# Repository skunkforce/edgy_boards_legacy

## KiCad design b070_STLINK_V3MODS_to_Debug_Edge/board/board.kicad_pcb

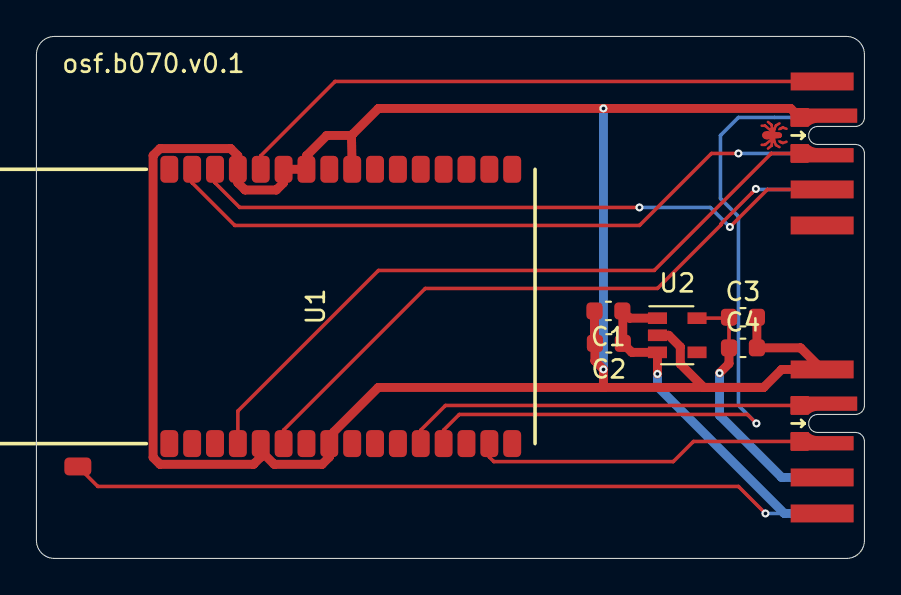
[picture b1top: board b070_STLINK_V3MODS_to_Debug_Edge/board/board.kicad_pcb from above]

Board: 2 copper layers, 46.0 x 29.0 mm, 8 parts (0 on the bottom side), 11 nets.

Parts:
C1: 100nF; C_0603_1608Metric
C2, C4: 1uF; C_0603_1608Metric
C3: 10uF; C_0603_1608Metric
J1: DebugEdge_02x05; debug_edge_2x05_host
J2: 010_UART; on_edge_2x05_host
U1: STLINK-V3MODS; stlink-v3mods
U2: TC1017-xCT; SOT-23-5

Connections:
+3V3: C3.1, C4.1, J2.9, U2.5
+5V: C1.1, C2.1, J2.10, U1.33, U2.1, U2.3
GND: C1.2, C2.2, C3.2, C4.2, J1.1, J2.1, U1.5, U1.8, U1.24, U1.26, U1.27, U1.29, U2.2
unnamed: J1.2, U1.4
unnamed: J1.3, U1.13
unnamed: J1.4, U1.31
unnamed: J1.5, U1.30
unnamed: J1.6, U1.6
unnamed: J1.7, U1.28
unnamed: J2.2, U1.12
unnamed: J2.3, U1.15

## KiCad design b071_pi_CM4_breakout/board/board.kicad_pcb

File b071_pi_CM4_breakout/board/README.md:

# pi Compute Module 4 breakout

## Setting up the CM4 as a remote edgy composition gateway
One important use case of edgyboards is to fascilitate unit testing and CI style development near the metal by effectivly mocking out parts of the hardware.

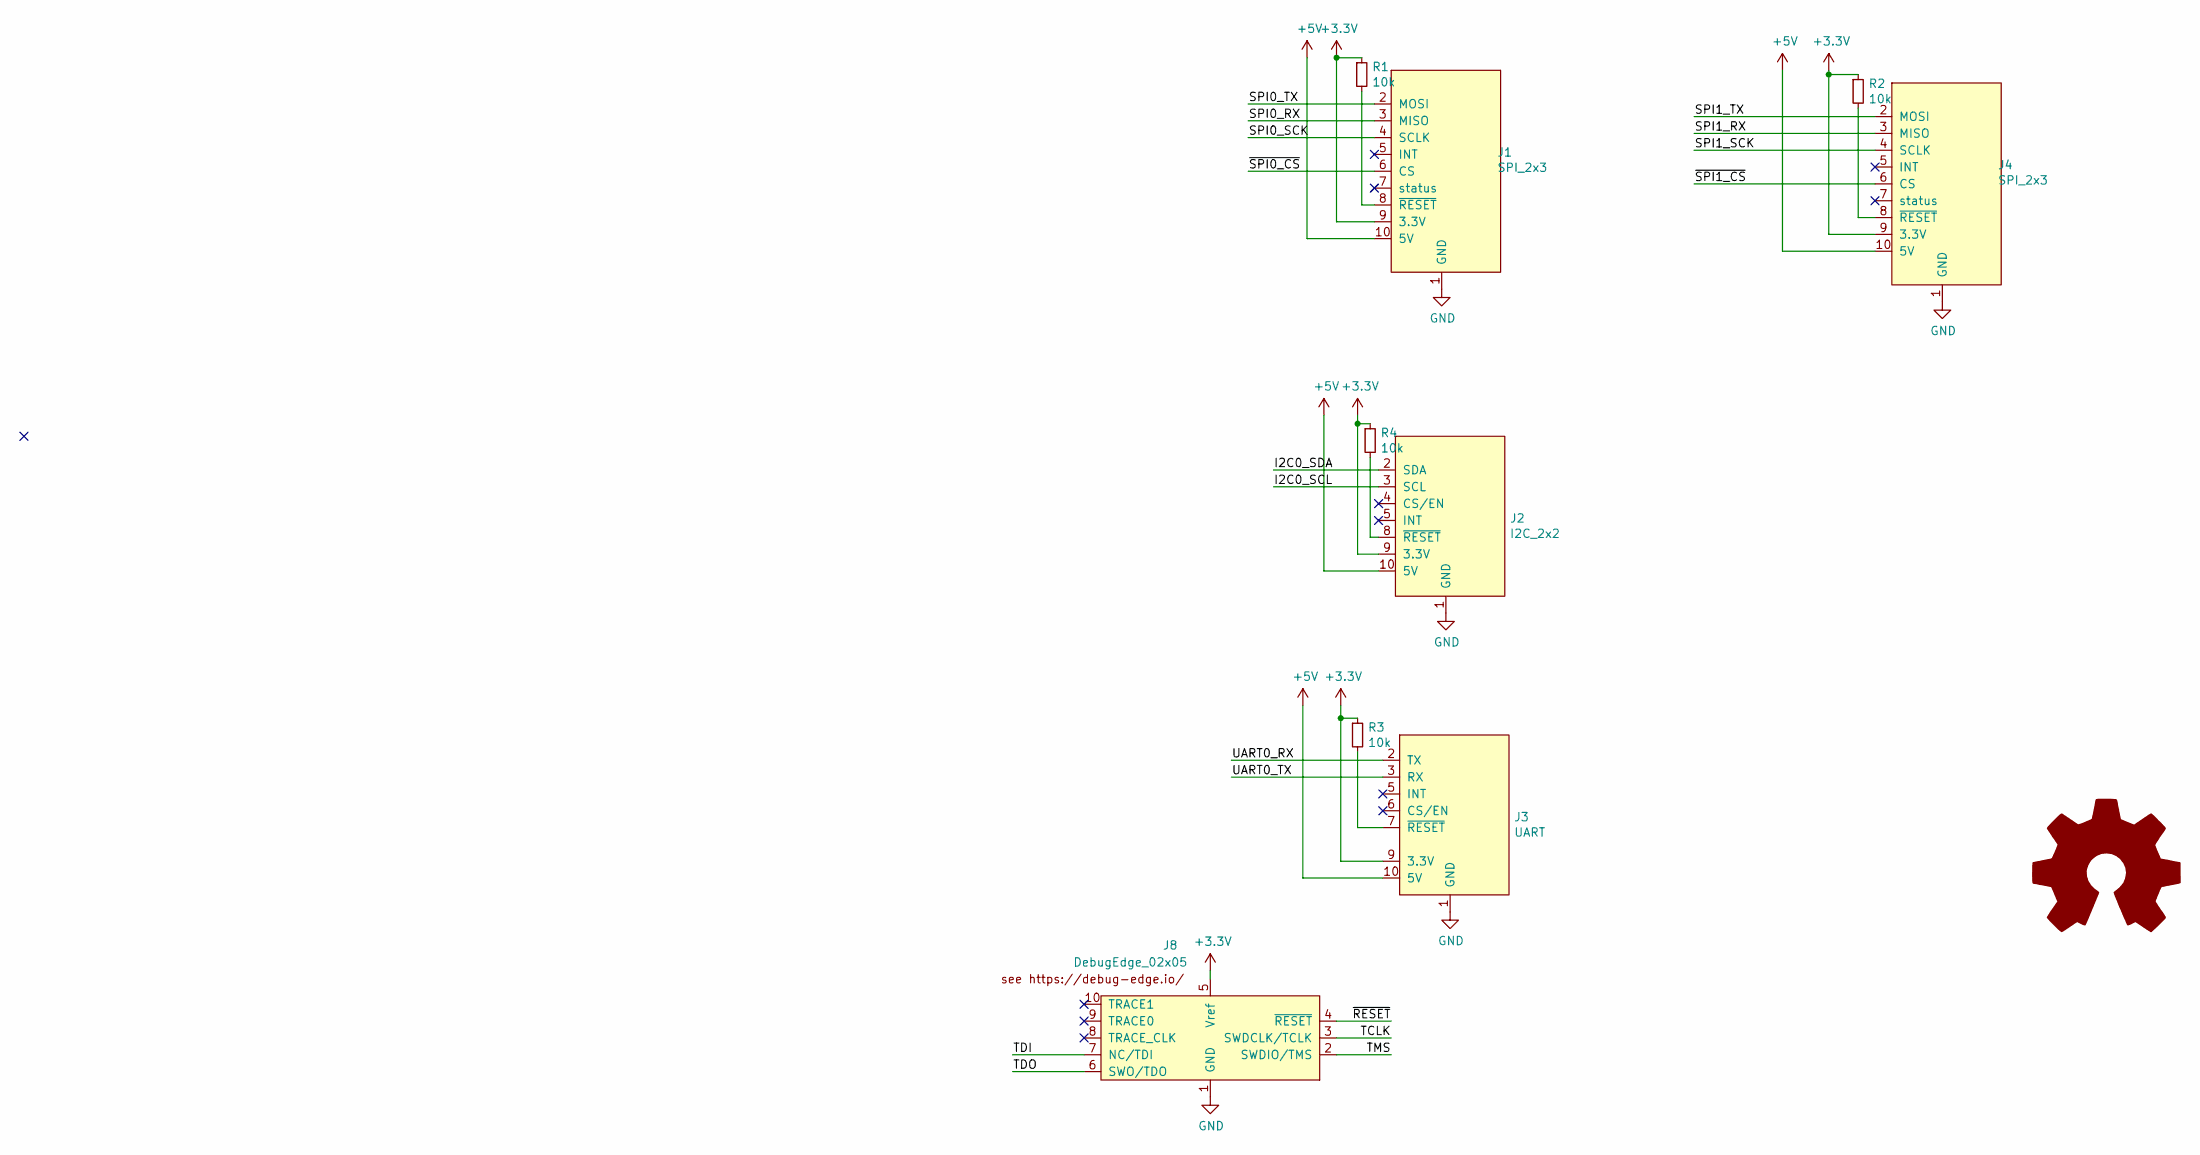
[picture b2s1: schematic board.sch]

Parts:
J1: SPI_2x3; on_edge_2x05_up_host
J2: I2C_2x2; on_edge_2x05_host
J3: UART; on_edge_2x05_host
J4: SPI_2x3; on_edge_2x05_host
J8: DebugEdge_02x05; debug_edge_2x05_host
R1, R2, R3, R4: 10k; R_0603_1608Metric
l1: Logo_Open_Hardware_Large; OSHW-Logo2_7.3x6mm_SilkScreen

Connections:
+3V3: J1.9 (3.3V), J2.9 (3.3V), J3.9 (3.3V), J4.9 (3.3V), J8.5 (Vref), R1.1, R2.1, R3.1, R4.1
+5V: J1.10 (5V), J2.10 (5V), J3.10 (5V), J4.10 (5V)
/I2C0_SCL: J2.3 (SCL)
/I2C0_SDA: J2.2 (SDA)
/SPI0_RX: J1.3 (MISO)
/SPI0_SCK: J1.4 (SCLK)
/SPI0_TX: J1.2 (MOSI)
/SPI1_RX: J4.3 (MISO)
/SPI1_SCK: J4.4 (SCLK)
/SPI1_TX: J4.2 (MOSI)
/TCLK: J8.3 (SWDCLK/TCLK)
/TDI: J8.7 (NC/TDI)
/TDO: J8.6 (SWO/TDO)
/TMS: J8.2 (SWDIO/TMS)
/UART0_RX: J3.2 (TX)
/UART0_TX: J3.3 (RX)
/~RESET: J8.4 (~RESET~)
/~SPI0_CS: J1.6 (CS)
/~SPI1_CS: J4.6 (CS)
GND: J1.1 (GND), J2.1 (GND), J3.1 (GND), J4.1 (GND), J8.1 (GND)
unnamed: J1.8 (~RESET), R1.2
unnamed: J2.8 (~RESET), R4.2
unnamed: J3.7 (~RESET), R3.2
unnamed: J4.8 (~RESET), R2.2

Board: 2 copper layers, 10 parts (1 on the bottom side), 7 nets, no tracks yet.

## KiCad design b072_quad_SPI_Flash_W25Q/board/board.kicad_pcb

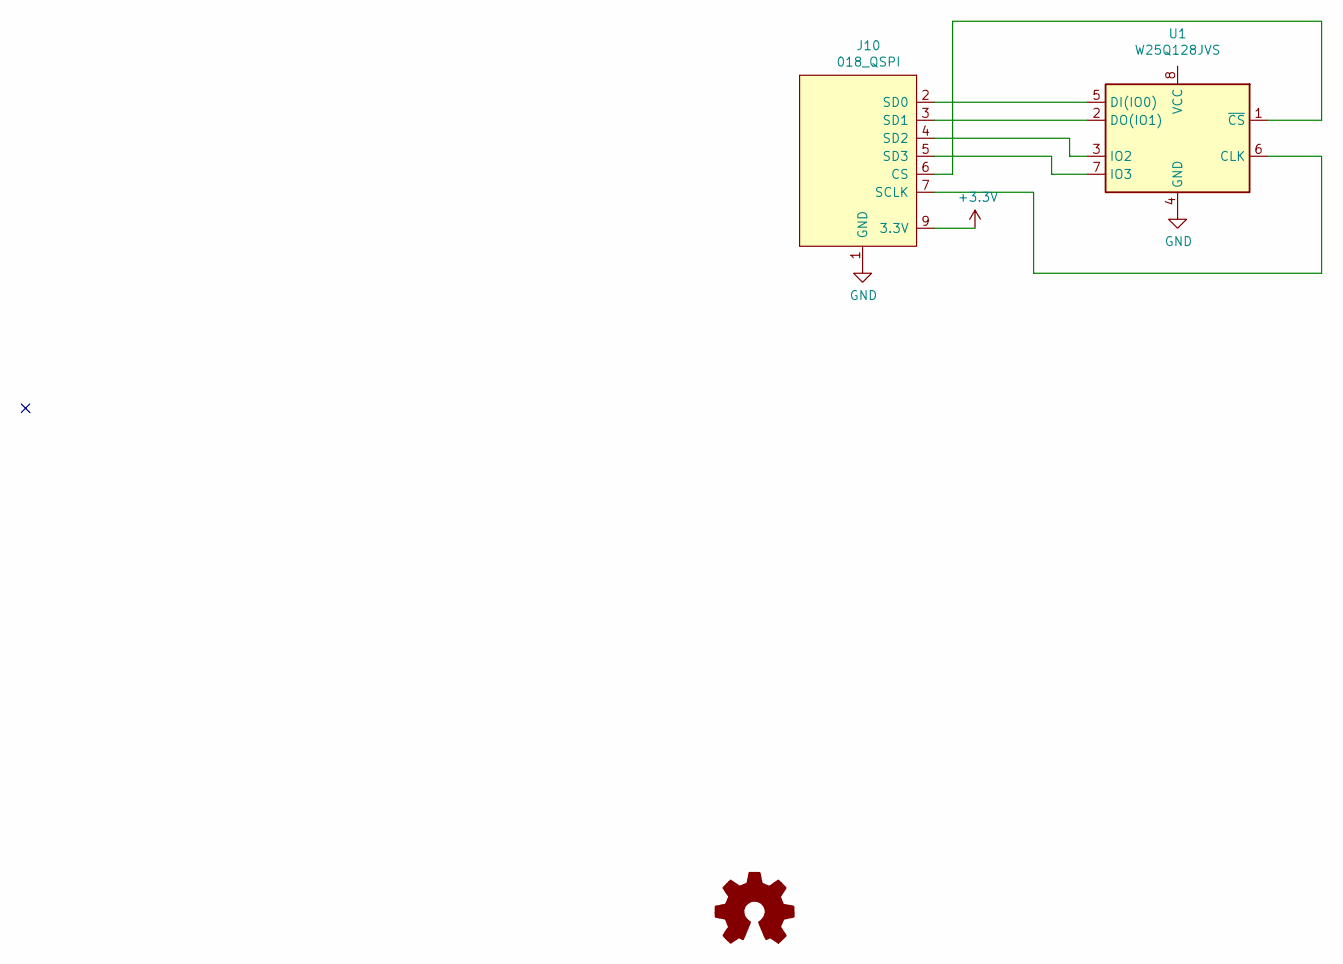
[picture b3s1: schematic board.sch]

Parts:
J10: 018_QSPI; on_edge_2x05_device
LOGO1: Logo_Open_Hardware_Small; OSHW-Logo2_9.8x8mm_SilkScreen
U1: W25Q128JVS; SOIC-8_5.23x5.23mm_P1.27mm; MPN W25Q16JVSNIQ

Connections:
+3V3: J10.9 (3.3V)
GND: J10.1 (GND), U1.4 (GND)
unnamed: J10.2 (SD0), U1.5 (DI(IO0))
unnamed: J10.3 (SD1), U1.2 (DO(IO1))
unnamed: J10.4 (SD2), U1.3 (IO2)
unnamed: J10.5 (SD3), U1.7 (IO3)
unnamed: J10.6 (CS), U1.1 (~CS)
unnamed: J10.7 (SCLK), U1.6 (CLK)

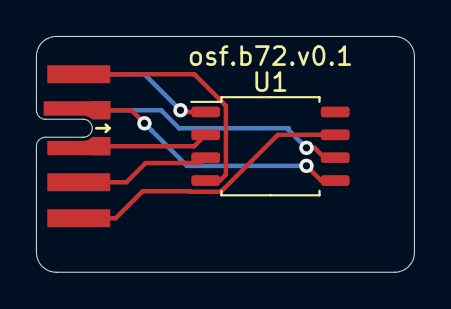
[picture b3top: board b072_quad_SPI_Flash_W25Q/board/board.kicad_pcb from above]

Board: 4 copper layers, 21.0 x 13.1 mm, 3 parts (1 on the bottom side), 7 nets.

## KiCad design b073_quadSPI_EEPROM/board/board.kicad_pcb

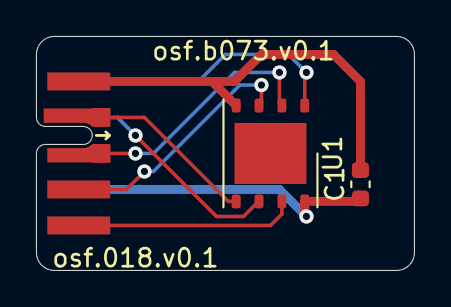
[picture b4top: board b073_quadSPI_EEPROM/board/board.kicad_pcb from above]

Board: 2 copper layers, 21.0 x 13.0 mm, 3 parts (0 on the bottom side), 8 nets.

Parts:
C1: 100nF; C_0603_1608Metric
J1: 018_QSPI; on_edge_2x05_device
U1: W25Q32JVSS; WSON-8-1EP_6x5mm_P1.27mm_EP3.4x4mm

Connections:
GND: C1.2, J1.1 (GND), U1.4 (GND)
unnamed: C1.1, J1.9 (3.3V), U1.8 (VCC)
unnamed: J1.2 (SD0), U1.5 (DI(IO0))
unnamed: J1.3 (SD1), U1.2 (DO(IO1))
unnamed: J1.4 (SD2), U1.3 (IO2)
unnamed: J1.5 (SD3), U1.7 (IO3)
unnamed: J1.6 (CS), U1.1 (~CS)
unnamed: J1.7 (SCLK), U1.6 (CLK)

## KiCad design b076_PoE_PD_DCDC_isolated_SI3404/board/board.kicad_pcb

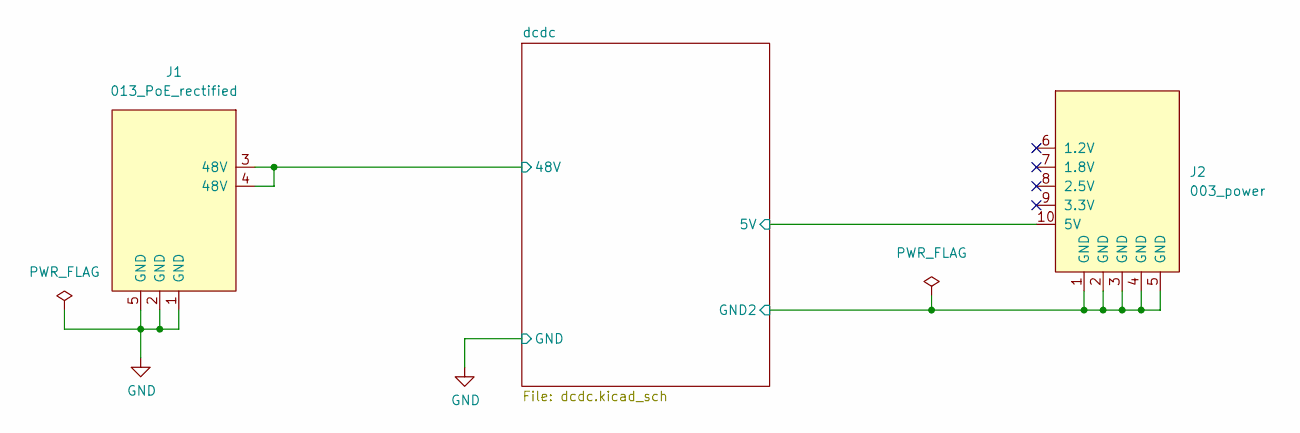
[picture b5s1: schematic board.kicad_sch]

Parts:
J1: 013_PoE_rectified; on_edge_2x05_device
J2: 003_power; on_edge_2x05_host

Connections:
/dcdc/5V: J2.10 (5V); also elsewhere on the board
/dcdc/48V: J1.3 (48V), J1.4 (48V); also elsewhere on the board
/dcdc/GND2: J2.1 (GND), J2.2 (GND), J2.3 (GND), J2.4 (GND), J2.5 (GND); also elsewhere on the board
GND: J1.1 (GND), J1.2 (GND), J1.5 (GND); also elsewhere on the board

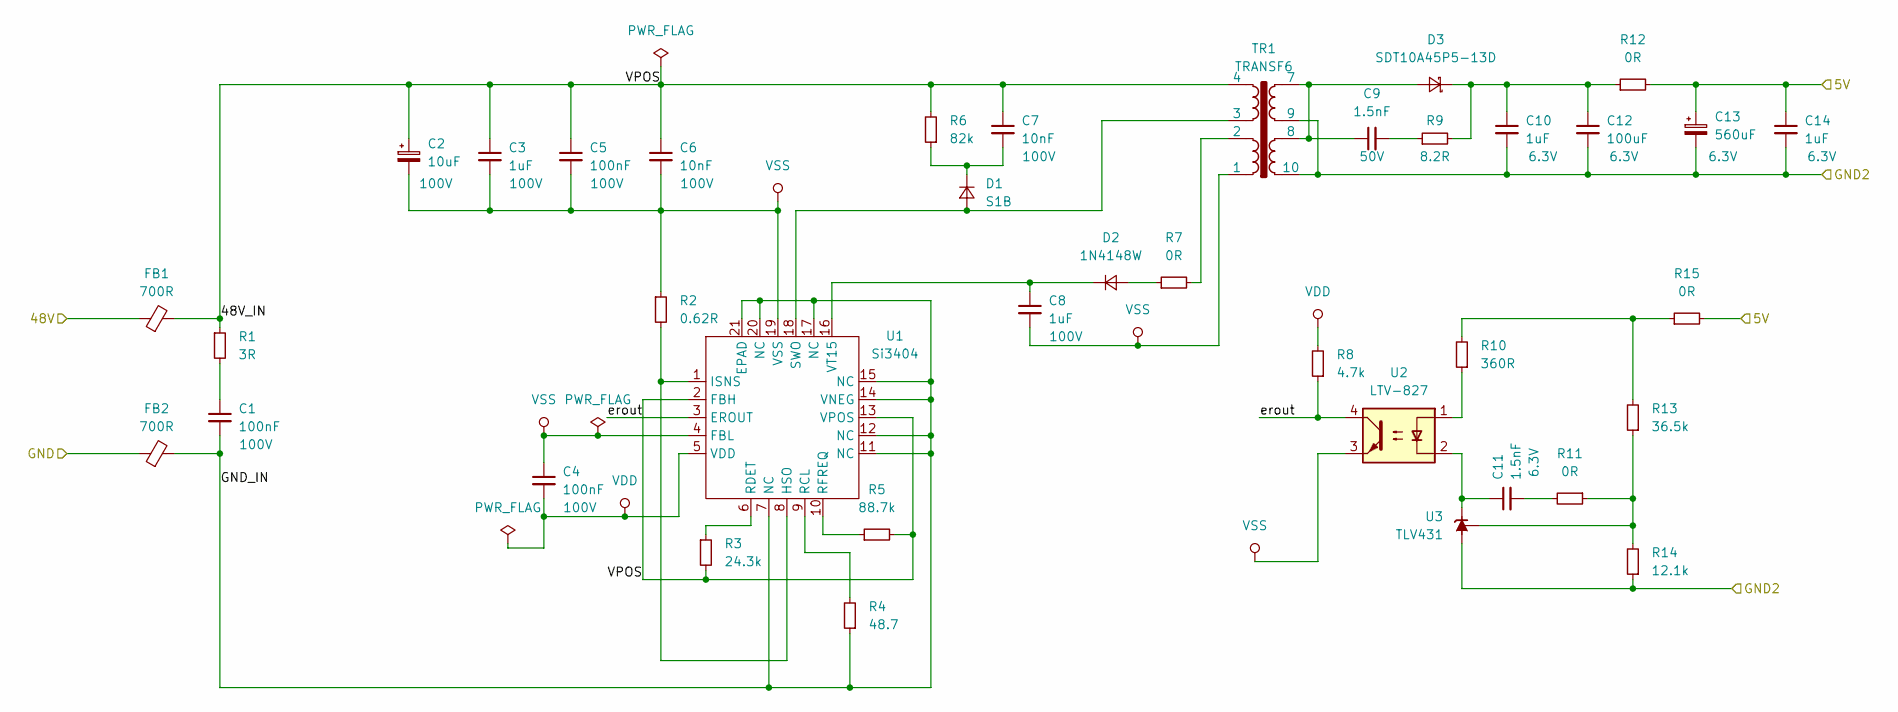
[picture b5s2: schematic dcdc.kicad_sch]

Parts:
C1, C5: 100nF; C_1210_3225Metric; Voltage 100V
C2: 10uF; CP_Elec_10x10; Voltage 100V
C3, C8: 1uF; C_1210_3225Metric; Voltage 100V
C4: 100nF; C_0603_1608Metric; Voltage 100V
C6, C7: 10nF; C_1210_3225Metric; Voltage 100V
C9: 1.5nF; C_0805_2012Metric; Voltage 50V
C10, C14: 1uF; C_0603_1608Metric; Voltage 6.3V
C11: 1.5nF; C_0603_1608Metric; Voltage 6.3V
C12: 100uF; C_0805_2012Metric; Voltage 6.3V
C13: 560uF; CP_Elec_10x10; Voltage 6.3V
D1: S1B; D_SMB
D2: 1N4148W; D_SOD-123; MPN 1N4148W-HF
D3: SDT10A45P5-13D; D_PowerDI-5; MPN SDT10A45P5-13D
FB1, FB2: 700R; L_0805_2012Metric; MPN 742792040
R1: 3R; R_0603_1608Metric
R2: 0.62R; R_0805_2012Metric
R3: 24.3k; R_0603_1608Metric
R4: 48.7; R_0603_1608Metric
R5: 88.7k; R_0603_1608Metric
R6: 82k; R_0603_1608Metric
R7, R11, R15: 0R; R_0603_1608Metric
R8: 4.7k; R_0603_1608Metric
R9: 8.2R; R_0603_1608Metric
R10: 360R; R_0603_1608Metric
R12: 0R; R_1210_3225Metric
R13: 36.5k; R_0603_1608Metric
R14: 12.1k; R_0603_1608Metric
TR1: TRANSF6; EP13_SMT_H_10PIN_(2381); MPN 749119950
U1: Si3404; QFN-20-1EP_4x4mm_P0.5mm_EP2.5x2.5mm_ThermalVias; MPN SI3404-A-GM
U2: LTV-827; DIP-8_W7.62mm; MPN FOD817A3SD
U3: TLV431; SOT-23; MPN TLV431CSN1T1G

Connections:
/dcdc/5V: C13.1, C14.1, R12.2, R15.2; also elsewhere on the board
/dcdc/48V: FB1.1; also elsewhere on the board
/dcdc/48V_IN: C2.1, C3.1, C5.1, C6.1, C7.1, FB1.2, R1.1, R3.2, R5.2, R6.2, TR1.4, U1.2 (FBH), U1.13 (VPOS)
/dcdc/GND2: C10.2, C12.2, C13.2, C14.2, R14.1, TR1.9, TR1.10, U3.3 (A); also elsewhere on the board
/dcdc/GND_IN: C1.2, FB2.2, R4.1, U1.7 (NC), U1.11 (NC), U1.12 (NC), U1.14 (VNEG), U1.15 (NC), U1.17 (NC), U1.20 (NC), U1.21 (EPAD)
/dcdc/erout: R8.1, U1.3 (EROUT), U2.4
GND: FB2.1; also elsewhere on the board
unnamed: C1.1, R1.2
unnamed: C7.2, D1.1 (K), R6.1
unnamed: C8.1, D2.1 (K), U1.16 (VT15)
unnamed: C9.1, D3.2 (A), TR1.7, TR1.8
unnamed: C9.2, R9.1
unnamed: C10.1, C12.1, D3.1 (K), R9.2, R12.1
unnamed: C11.1, U2.2, U3.1 (K)
unnamed: C11.2, R11.2
unnamed: D1.2 (A), TR1.3, U1.18 (SWO)
unnamed: D2.2 (A), R7.1
unnamed: R2.2, U1.1 (ISNS), U1.8 (HSO)
unnamed: R3.1, U1.6 (RDET)
unnamed: R4.2, U1.9 (RCL)
unnamed: R5.1, U1.10 (RFREQ)
unnamed: R7.2, TR1.2
unnamed: R10.1, U2.1
unnamed: R10.2, R13.2, R15.1
unnamed: R11.1, R13.1, R14.2, U3.2 (REF)
VDD: C4.2, R8.2, U1.5 (VDD)
VSS: C2.2, C3.2, C4.1, C5.2, C6.2, C8.2, R2.1, TR1.1, U1.4 (FBL), U1.19 (VSS), U2.3

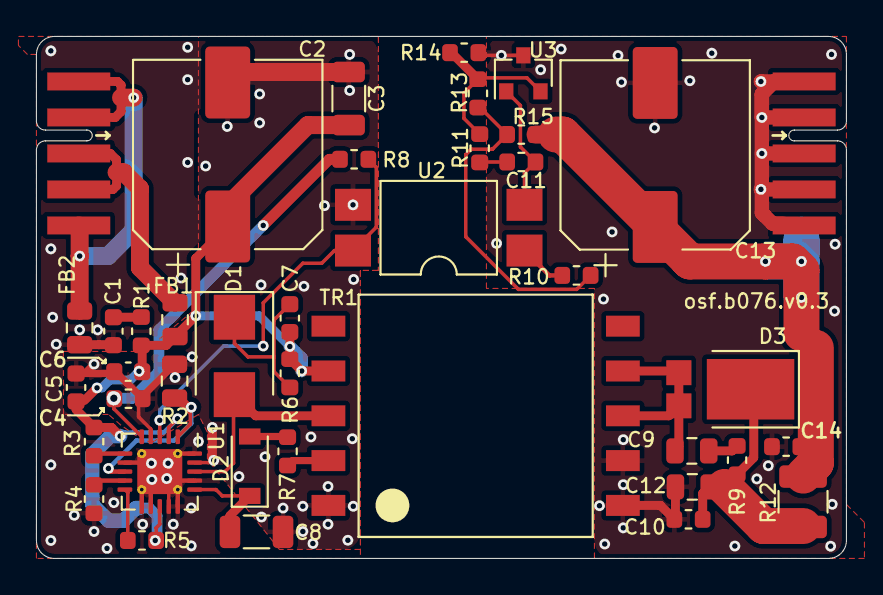
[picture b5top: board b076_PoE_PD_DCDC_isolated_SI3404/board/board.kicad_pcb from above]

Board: 2 copper layers, 45.0 x 29.0 mm, 40 parts (0 on the bottom side), 27 nets.

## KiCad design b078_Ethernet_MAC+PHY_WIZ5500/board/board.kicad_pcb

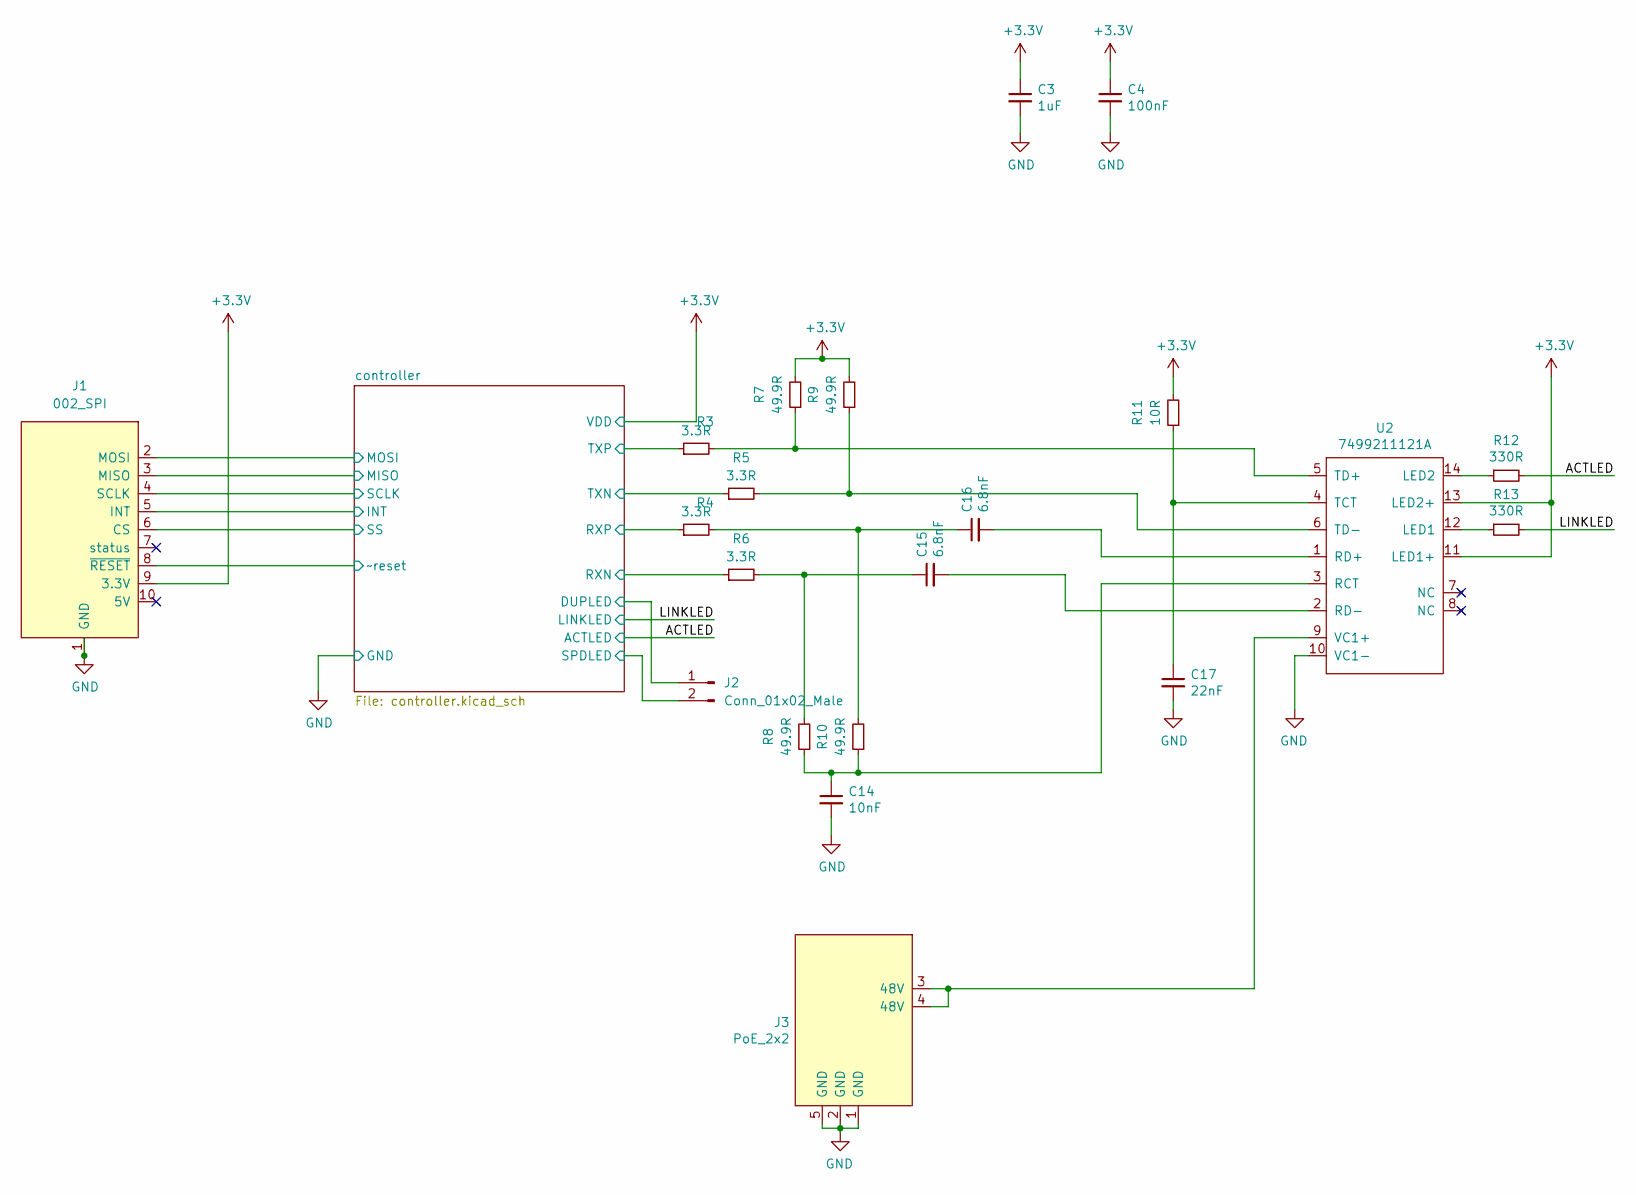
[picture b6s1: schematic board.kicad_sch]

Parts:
C3: 1uF; C_0603_1608Metric; Voltage 6.3V
C4: 100nF; C_0603_1608Metric; Voltage 6.3V
C14: 10nF; C_0603_1608Metric; Voltage 6.3V
C15, C16: 6.8nF; C_0603_1608Metric; Voltage 6.3V
C17: 22nF; C_0603_1608Metric; Voltage 6.3V
J1: 002_SPI; on_edge_2x05_device
J2: Conn_01x02_Male; PinHeader_1x02_P2.54mm_Vertical
J3: PoE_2x2; on_edge_2x05_host
R3, R4, R5, R6: 3.3R; R_0603_1608Metric
R7, R8, R9, R10: 49.9R; R_0805_2012Metric
R11: 10R; R_0805_2012Metric
R12, R13: 330R; R_0603_1608Metric
U2: 7499211121A; MPN 7499211121A

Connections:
+3V3: C3.1, C4.1, J1.9 (3.3V), R7.2, R9.2, R11.2, U2.11 (LED1+), U2.13 (LED2+); also elsewhere on the board
/ACTLED: R12.2; also elsewhere on the board
/LINKLED: R13.2; also elsewhere on the board
/controller/DUPLED: J2.1; also elsewhere on the board
/controller/INT: J1.5 (INT); also elsewhere on the board
/controller/MISO: J1.3 (MISO); also elsewhere on the board
/controller/MOSI: J1.2 (MOSI); also elsewhere on the board
/controller/RXN: R6.1; also elsewhere on the board
/controller/RXP: R4.1; also elsewhere on the board
/controller/SCLK: J1.4 (SCLK); also elsewhere on the board
/controller/SPDLED: J2.2; also elsewhere on the board
/controller/SS: J1.6 (CS); also elsewhere on the board
/controller/TXN: R5.1; also elsewhere on the board
/controller/TXP: R3.1; also elsewhere on the board
/controller/~reset: J1.8 (~RESET); also elsewhere on the board
GND: C3.2, C4.2, C14.2, C17.2, J1.1 (GND), J3.1 (GND), J3.2 (GND), J3.5 (GND), U2.10 (VC1-); also elsewhere on the board
unnamed: C14.1, R8.1, R10.1, U2.3 (RCT)
unnamed: C15.1, R6.2, R8.2
unnamed: C15.2, U2.2 (RD-)
unnamed: C16.1, R4.2, R10.2
unnamed: C16.2, U2.1 (RD+)
unnamed: C17.1, R11.1, U2.4 (TCT)
unnamed: J3.3 (48V), J3.4 (48V), U2.9 (VC1+)
unnamed: R3.2, R7.1, U2.5 (TD+)
unnamed: R5.2, R9.1, U2.6 (TD-)
unnamed: R12.1, U2.14 (LED2)
unnamed: R13.1, U2.12 (LED1)

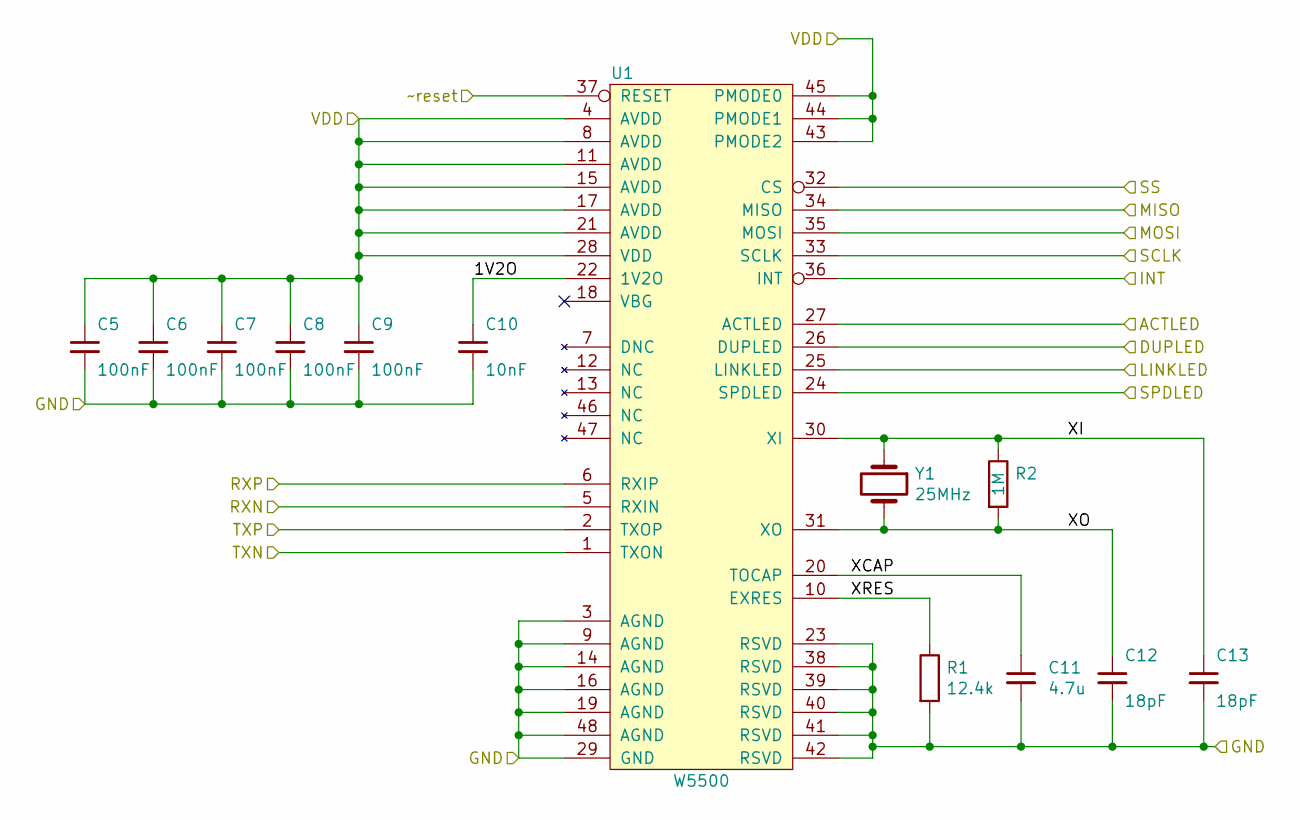
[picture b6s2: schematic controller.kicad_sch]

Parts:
C5, C6, C7, C8, C9: 100nF; C_0603_1608Metric; DigiKey Part Number 1276-1012-1-ND
C10: 10nF; C_0603_1608Metric; DigiKey Part Number 1276-1921-1-ND
C11: 4.7u; C_0603_1608Metric; DigiKey Part Number 1276-1907-1-ND
C12, C13: 18pF; C_0603_1608Metric; DigiKey Part Number 1276-1089-1-ND
R1: 12.4k; R_0603_1608Metric; Tolerance ±1%; DigiKey Part Number 311-12.4KHRCT-ND
R2: 1M; R_0603_1608Metric; DigiKey Part Number 311-1.0MGRCT-ND
U1: W5500; LQFP-48_7x7mm_P0.5mm; DigiKey Part Number 1278-1021-ND
Y1: 25MHz; Crystal_SMD_5032-2Pin_5.0x3.2mm; MPN 445I23D25M00000; DigiKey Part Number CTX1175TR-ND

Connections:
+3V3: C5.1, C6.1, C7.1, C8.1, C9.1, U1.4 (AVDD), U1.8 (AVDD), U1.11 (AVDD), U1.15 (AVDD), U1.17 (AVDD), U1.21 (AVDD), U1.28 (VDD), U1.43 (PMODE2), U1.44 (PMODE1), U1.45 (PMODE0); also elsewhere on the board
/ACTLED: U1.27 (ACTLED); also elsewhere on the board
/LINKLED: U1.25 (LINKLED); also elsewhere on the board
/controller/1V2O: C10.1, U1.22 (1V2O)
/controller/DUPLED: U1.26 (DUPLED); also elsewhere on the board
/controller/INT: U1.36 (INT); also elsewhere on the board
/controller/MISO: U1.34 (MISO); also elsewhere on the board
/controller/MOSI: U1.35 (MOSI); also elsewhere on the board
/controller/RXN: U1.5 (RXIN); also elsewhere on the board
/controller/RXP: U1.6 (RXIP); also elsewhere on the board
/controller/SCLK: U1.33 (SCLK); also elsewhere on the board
/controller/SPDLED: U1.24 (SPDLED); also elsewhere on the board
/controller/SS: U1.32 (CS); also elsewhere on the board
/controller/TXN: U1.1 (TXON); also elsewhere on the board
/controller/TXP: U1.2 (TXOP); also elsewhere on the board
/controller/XCAP: C11.1, U1.20 (TOCAP)
/controller/XI: C13.1, R2.1, U1.30 (XI), Y1.1
/controller/XO: C12.1, R2.2, U1.31 (XO), Y1.2
/controller/XRES: R1.1, U1.10 (EXRES)
/controller/~reset: U1.37 (RESET); also elsewhere on the board
GND: C5.2, C6.2, C7.2, C8.2, C9.2, C10.2, C11.2, C12.2, C13.2, R1.2, U1.3 (AGND), U1.9 (AGND), U1.14 (AGND), U1.16 (AGND), U1.19 (AGND), U1.23 (RSVD), U1.29 (GND), U1.38 (RSVD), U1.39 (RSVD), U1.40 (RSVD), U1.41 (RSVD), U1.42 (RSVD), U1.48 (AGND); also elsewhere on the board

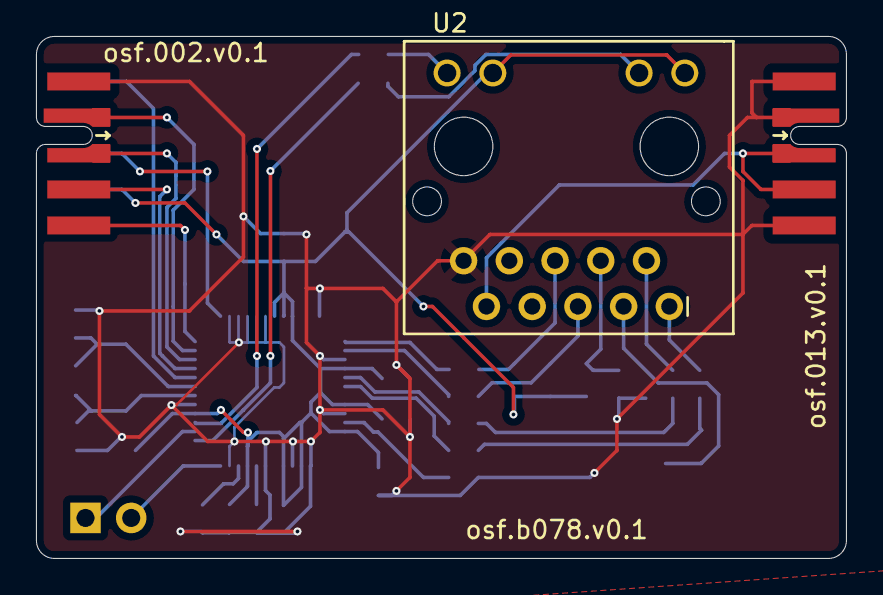
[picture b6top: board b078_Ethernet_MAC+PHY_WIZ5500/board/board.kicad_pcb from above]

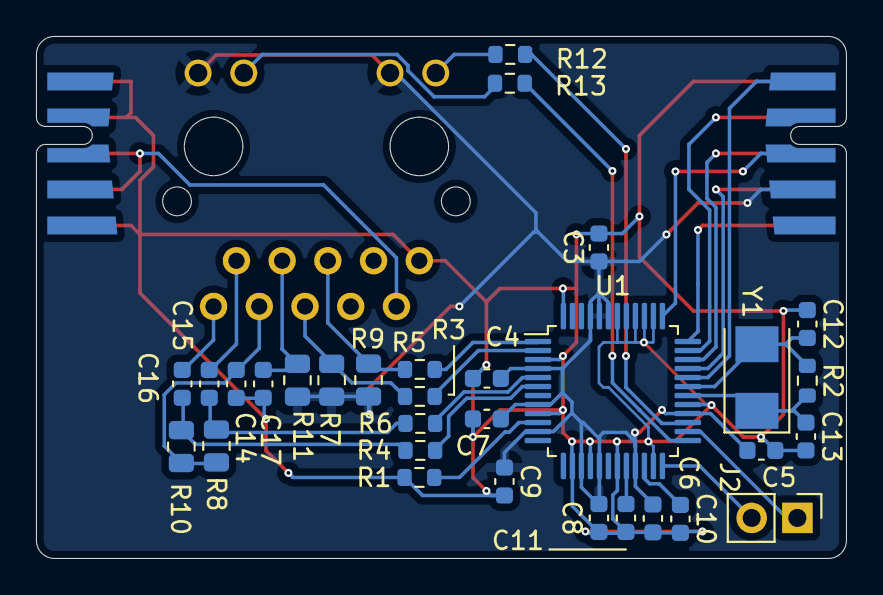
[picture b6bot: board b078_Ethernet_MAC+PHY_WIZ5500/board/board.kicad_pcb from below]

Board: 2 copper layers, 45.0 x 29.0 mm, 34 parts (31 on the bottom side), 32 nets.

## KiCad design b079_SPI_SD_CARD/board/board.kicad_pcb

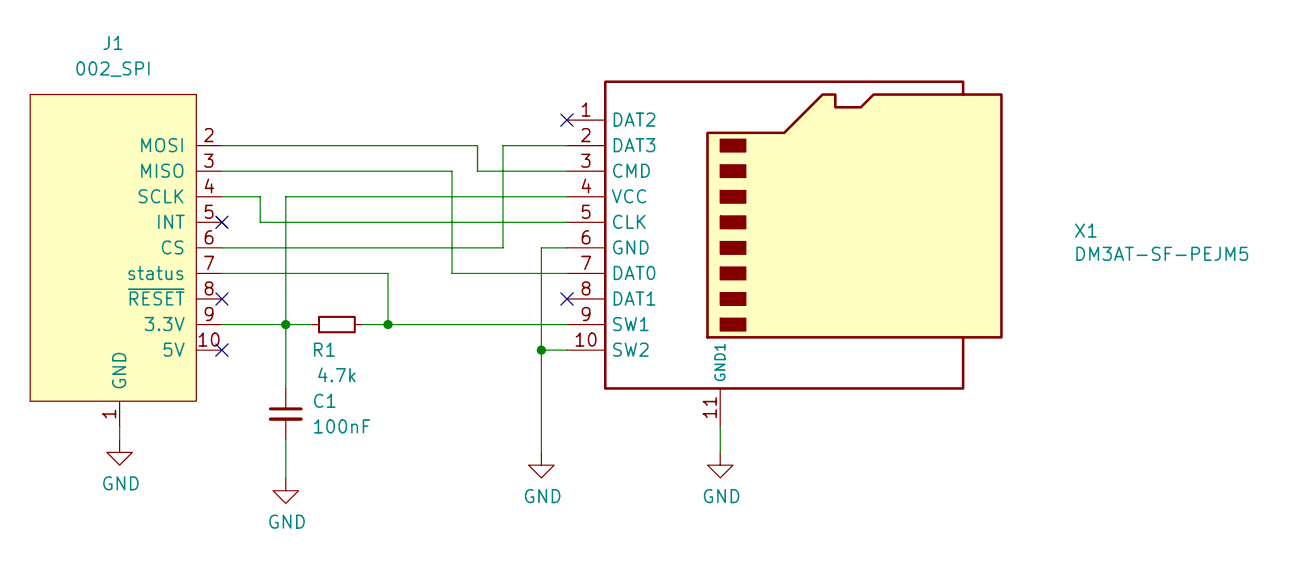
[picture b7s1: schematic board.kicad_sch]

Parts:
C1: 100nF; C_0603_1608Metric
J1: 002_SPI; on_edge_2x05_device
R1: 4.7k; R_0603_1608Metric
X1: DM3AT-SF-PEJM5; microSD_HC_Hirose_DM3AT-SF-PEJM5; MPN DM3AT-SF-PEJM5; Digikey HR1964CT-ND

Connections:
GND: C1.2, J1.1 (GND), X1.6 (GND), X1.10 (SW2), X1.11 (GND1)
unnamed: C1.1, J1.9 (3.3V), R1.1, X1.4 (VCC)
unnamed: J1.2 (MOSI), X1.3 (CMD)
unnamed: J1.3 (MISO), X1.7 (DAT0)
unnamed: J1.4 (SCLK), X1.5 (CLK)
unnamed: J1.6 (CS), X1.2 (DAT3)
unnamed: J1.7 (status), R1.2, X1.9 (SW1)

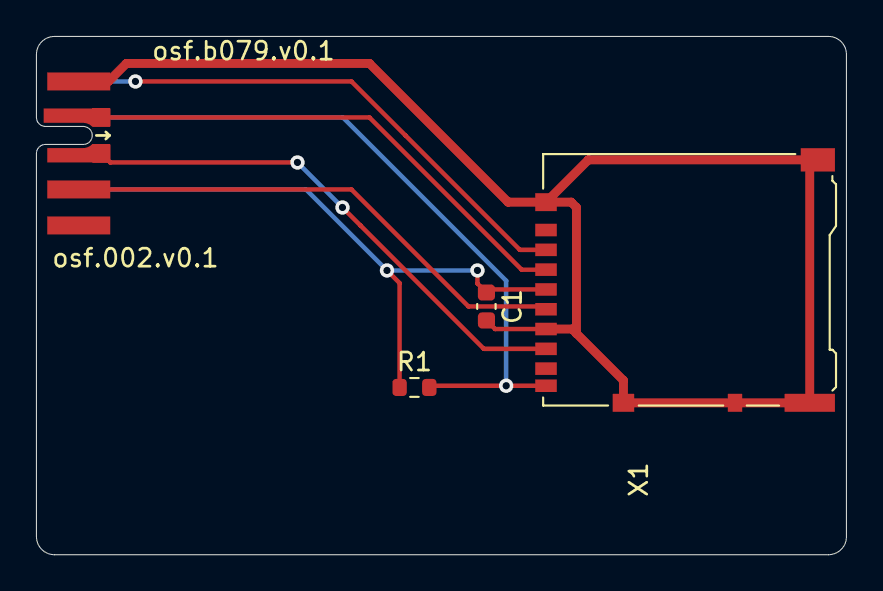
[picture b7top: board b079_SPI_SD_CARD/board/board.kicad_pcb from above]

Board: 2 copper layers, 45.0 x 28.8 mm, 4 parts (0 on the bottom side), 7 nets.

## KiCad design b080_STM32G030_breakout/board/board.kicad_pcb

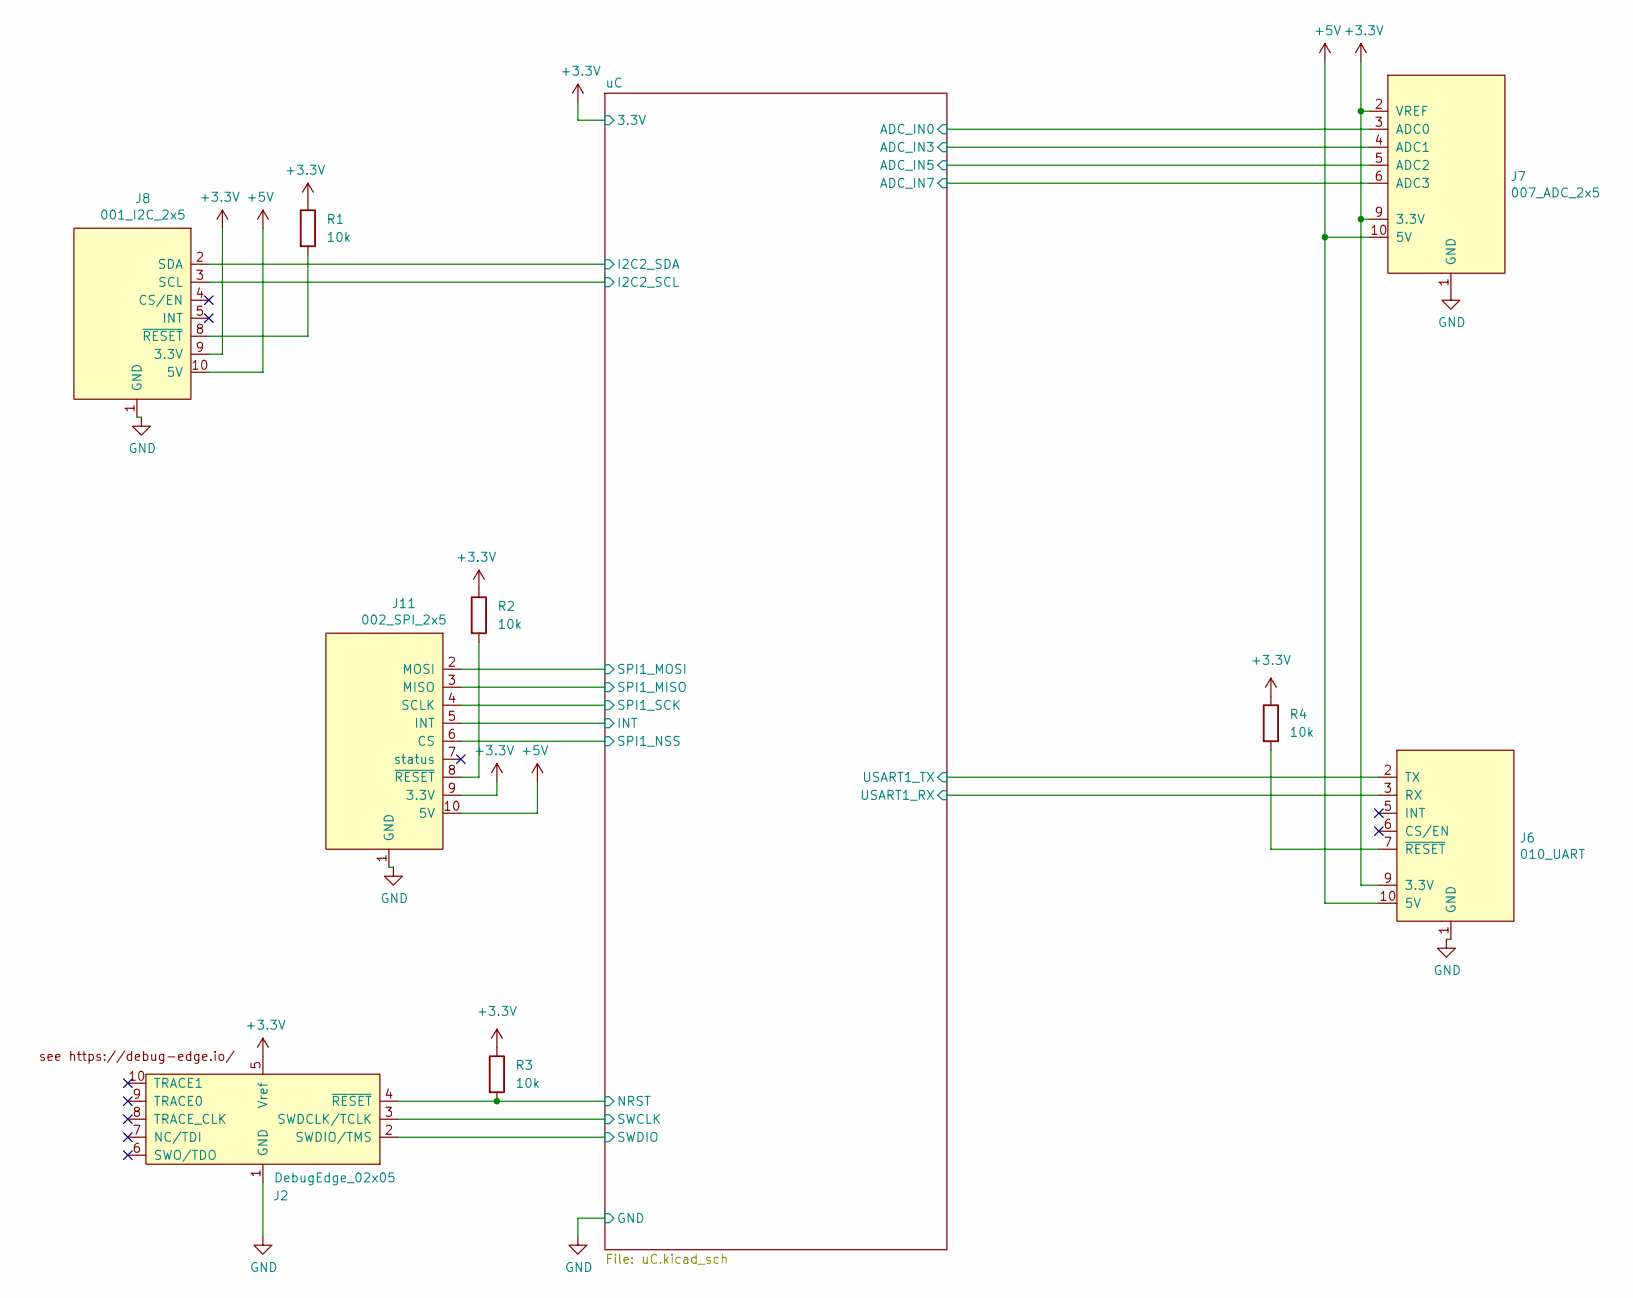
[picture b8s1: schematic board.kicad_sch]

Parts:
J2: DebugEdge_02x05; on_edge_2x05_device
J6: 010_UART; on_edge_2x05_up_host
J7: 007_ADC_2x5; on_edge_2x05_host
J8: 001_I2C_2x5; on_edge_2x05_up_host
J11: 002_SPI_2x5; on_edge_2x05_up_host
R1, R2, R3, R4: 10k; R_0603_1608Metric_Pad0.98x0.95mm_HandSolder

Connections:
+3V3: J2.5 (Vref), J6.9 (3.3V), J7.2 (VREF), J7.9 (3.3V), J8.9 (3.3V), J11.9 (3.3V), R1.1, R2.1, R3.1, R4.1; also elsewhere on the board
+5V: J6.10 (5V), J7.10 (5V), J8.10 (5V), J11.10 (5V)
/uC/ADC_IN0: J7.3 (ADC0); also elsewhere on the board
/uC/ADC_IN3: J7.4 (ADC1); also elsewhere on the board
/uC/ADC_IN5: J7.5 (ADC2); also elsewhere on the board
/uC/ADC_IN7: J7.6 (ADC3); also elsewhere on the board
/uC/I2C2_SCL: J8.3 (SCL); also elsewhere on the board
/uC/I2C2_SDA: J8.2 (SDA); also elsewhere on the board
/uC/INT: J11.5 (INT); also elsewhere on the board
/uC/NRST: J2.4 (~RESET), R3.2; also elsewhere on the board
/uC/SPI1_MISO: J11.3 (MISO); also elsewhere on the board
/uC/SPI1_MOSI: J11.2 (MOSI); also elsewhere on the board
/uC/SPI1_NSS: J11.6 (CS); also elsewhere on the board
/uC/SPI1_SCK: J11.4 (SCLK); also elsewhere on the board
/uC/SWCLK: J2.3 (SWDCLK/TCLK); also elsewhere on the board
/uC/SWDIO: J2.2 (SWDIO/TMS); also elsewhere on the board
/uC/USART1_RX: J6.3 (RX); also elsewhere on the board
/uC/USART1_TX: J6.2 (TX); also elsewhere on the board
GND: J2.1 (GND), J6.1 (GND), J7.1 (GND), J8.1 (GND), J11.1 (GND); also elsewhere on the board
unnamed: J6.7 (~RESET), R4.2
unnamed: J8.8 (~RESET), R1.2
unnamed: J11.8 (~RESET), R2.2
